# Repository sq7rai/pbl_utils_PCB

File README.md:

# pbl_utils_PCB
 Design of an PCB for testing PV panels.

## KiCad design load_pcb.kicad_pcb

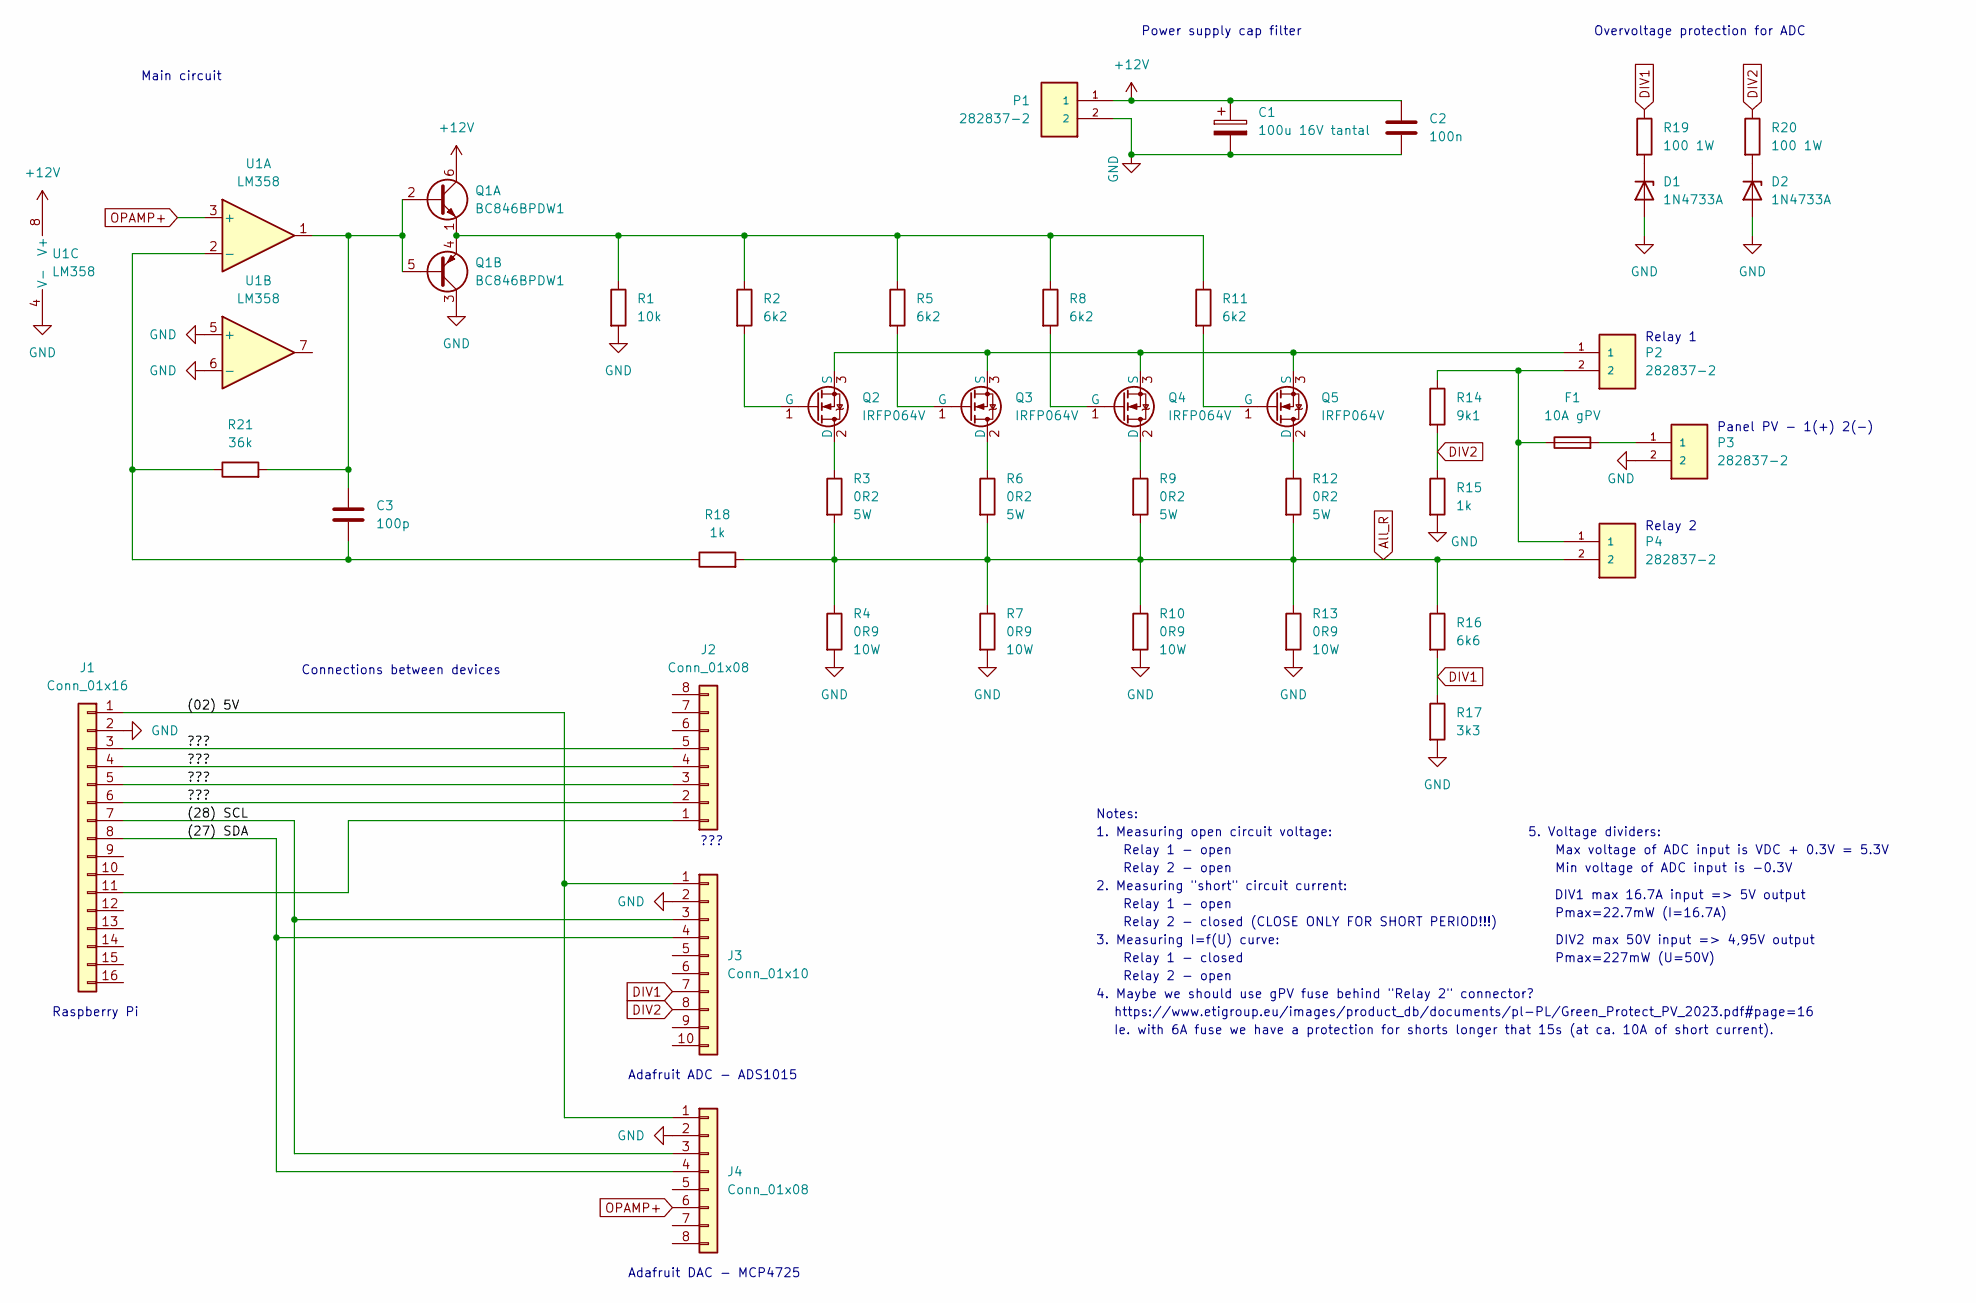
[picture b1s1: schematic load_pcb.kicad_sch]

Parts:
C1: 100u 16V tantal; CP_EIA-7343-31_Kemet-D_Pad2.25x2.55mm_HandSolder
C2: 100n; C_1206_3216Metric_Pad1.33x1.80mm_HandSolder
C3: 100p; C_1206_3216Metric_Pad1.33x1.80mm_HandSolder
D1, D2: 1N4733A; D_DO-41_SOD81_P3.81mm_Vertical_AnodeUp
F1: 10A gPV; Fuse_gPV_10.3x38mm
J1: Conn_01x16; PinSocket_1x16_P2.54mm_Vertical
J2, J4: Conn_01x08; PinSocket_1x08_P2.54mm_Vertical
J3: Conn_01x10; PinSocket_1x10_P2.54mm_Vertical
P1, P2, P3, P4: 282837-2; TE_282837-2
Q1: BC846BPDW1; DIP-6_W7.62mm_Socket
Q2, Q3, Q4, Q5: IRFP064V; TO-247-3_Vertical
R1: 10k; R_Axial_DIN0207_L6.3mm_D2.5mm_P10.16mm_Horizontal
R2, R5, R8, R11: 6k2; R_Axial_DIN0207_L6.3mm_D2.5mm_P10.16mm_Horizontal
R3, R6, R9, R12: 0R2; R_Axial_Power_L25.0mm_W9.0mm_P27.94mm
R4, R7, R10, R13: 0R9; R_Axial_Power_L50.0mm_W9.0mm_P60.96mm
R14: 9k1; R_Axial_DIN0207_L6.3mm_D2.5mm_P10.16mm_Horizontal
R15, R18: 1k; R_Axial_DIN0207_L6.3mm_D2.5mm_P10.16mm_Horizontal
R16: 6k6; R_Axial_DIN0207_L6.3mm_D2.5mm_P10.16mm_Horizontal
R17: 3k3; R_Axial_DIN0207_L6.3mm_D2.5mm_P10.16mm_Horizontal
R19, R20: 100 1W; R_Axial_DIN0309_L9.0mm_D3.2mm_P15.24mm_Horizontal
R21: 36k; R_Axial_DIN0207_L6.3mm_D2.5mm_P10.16mm_Horizontal
U1: LM358; DIP-8_W7.62mm_Socket_LongPads

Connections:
+12V: C1.1, C2.1, P1.1, Q1.6 (C1), U1.8 (V+)
/(02) 5V: J1.1, J3.1, J4.1
/(27) SDA: J1.8, J3.4, J4.4
/(28) SCL: J1.7, J3.3, J4.3
/???: J1.3, J1.4, J1.5, J1.6, J2.2, J2.3, J2.4, J2.5
All_R: P4.2, R3.2, R4.1, R6.2, R7.1, R9.2, R10.1, R12.2, R13.1, R16.1, R18.2
DIV1: J3.7, R16.2, R17.1, R19.1
DIV2: J3.8, R14.2, R15.1, R20.1
GND: C1.2, C2.2, D1.2 (A), D2.2 (A), J1.2, J3.2, J4.2, P1.2, P3.2, Q1.3 (C2), R1.2, R4.2, R7.2, R10.2, R13.2, R15.2, R17.2, U1.4 (V-), U1.5 (+), U1.6 (-)
unnamed: C3.1, Q1.2 (B1), Q1.5 (B2), R21.2, U1.1
unnamed: C3.2, R18.1, R21.1, U1.2 (-)
unnamed: D1.1 (K), R19.2
unnamed: D2.1 (K), R20.2
unnamed: F1.1, P2.2, P4.1, R14.1
unnamed: F1.2, P3.1
unnamed: J1.11, J2.1
unnamed: P2.1, Q2.3 (S), Q3.3 (S), Q4.3 (S), Q5.3 (S)
unnamed: Q1.1 (E1), Q1.4 (E2), R1.1, R2.1, R5.1, R8.1, R11.1
unnamed: Q2.1 (G), R2.2
unnamed: Q2.2 (D), R3.1
unnamed: Q3.1 (G), R5.2
unnamed: Q3.2 (D), R6.1
unnamed: Q4.1 (G), R8.2
unnamed: Q4.2 (D), R9.1
unnamed: Q5.1 (G), R11.2
unnamed: Q5.2 (D), R12.1
OPAMP+: J4.6, U1.3 (+)

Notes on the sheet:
Pmax=227mW (U=50V)
Raspberry Pi
Pmax=22.7mW (I=16.7A)
https://www.etigroup.eu/images/product_db/documents/pl-PL/Green_Protect_PV_2023.pdf#page=16
Relay 1
Adafruit ADC - ADS1015
Relay 1 - open
1. Measuring open circuit voltage:
5. Voltage dividers:
Relay 1 - closed
Power supply cap filter
Relay 2 - open
Relay 2
???
Ie. with 6A fuse we have a protection for shorts longer that 15s (at ca. 10A of short current).
Min voltage of ADC input is -0.3V
DIV1 max 16.7A input => 5V output
Notes:
Relay 2 - closed (CLOSE ONLY FOR SHORT PERIOD!!!)
Panel PV - 1(+) 2(-)
Main circuit
2. Measuring "short" circuit current:
Connections between devices
3. Measuring I=f(U) curve:
Max voltage of ADC input is VDC + 0.3V = 5.3V
Adafruit DAC - MCP4725
4. Maybe we should use gPV fuse behind "Relay 2" connector?
DIV2 max 50V input => 4,95V output
Overvoltage protection for ADC

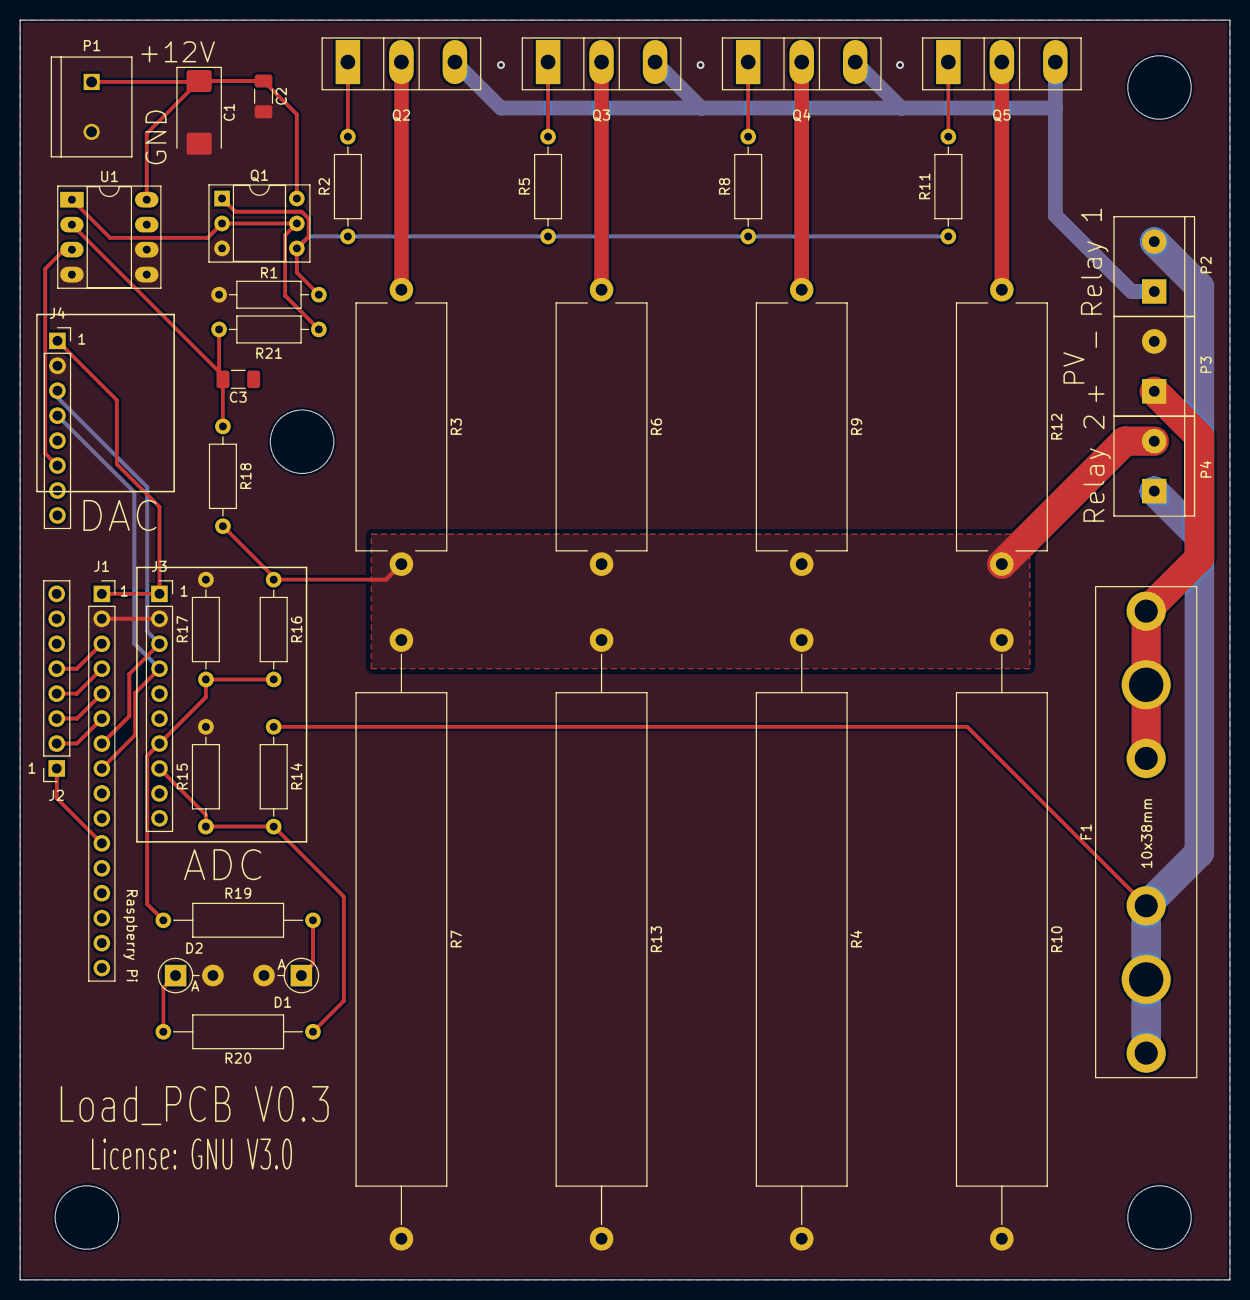
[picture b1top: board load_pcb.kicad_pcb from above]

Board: 2 copper layers, 123.2 x 128.3 mm, 41 parts (0 on the bottom side), 27 nets.

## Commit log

2023-03-21 Initial commit - update files
    Upload of all files
2023-03-23 Changed positions of connectors
2023-03-23 Added DAC and corrected positions of SMD/THD
2023-03-24 Small changes
    Corrected values of resistors in voltage dividers and added overvoltage protection for ADC inputs.
2023-04-20 Add a simulation in LTspice and production files

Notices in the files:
load_pcb.kicad_pcb:
License: GNU V3.0
